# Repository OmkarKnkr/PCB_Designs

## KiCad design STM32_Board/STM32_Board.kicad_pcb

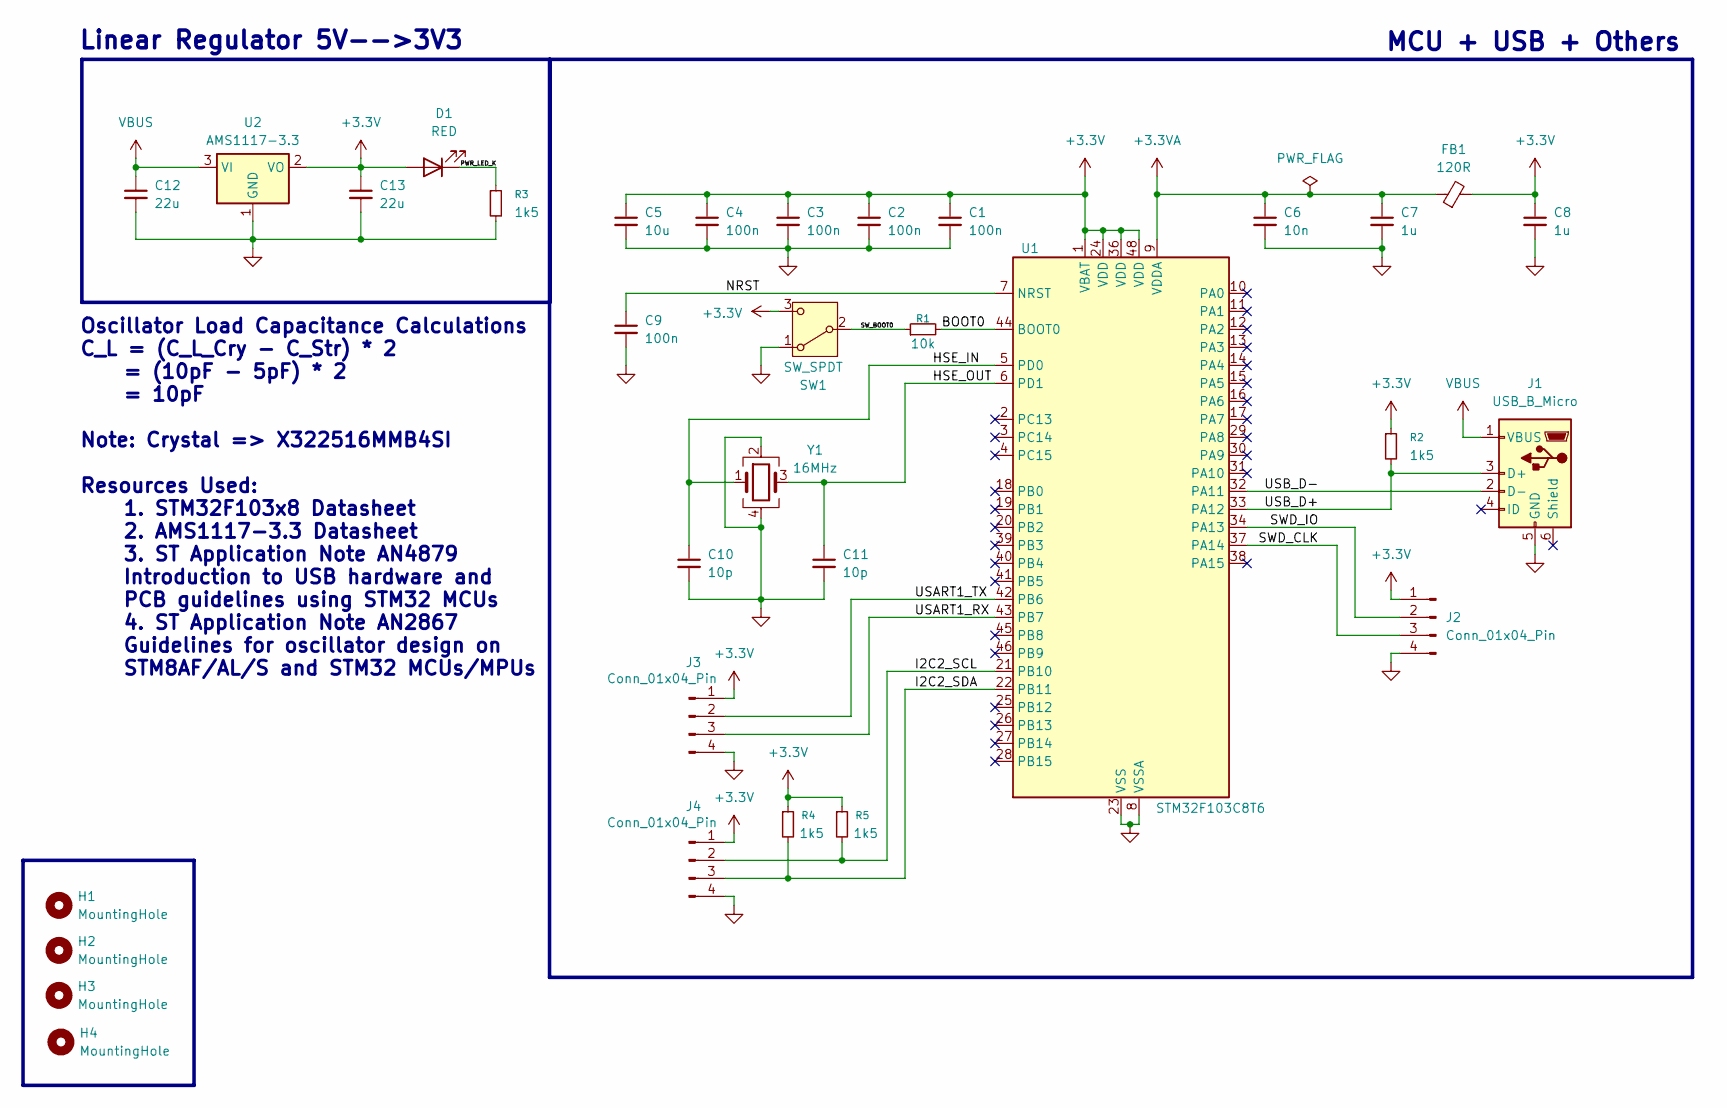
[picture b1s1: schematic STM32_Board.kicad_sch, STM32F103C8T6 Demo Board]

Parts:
C1, C2, C3, C4, C9: 100n; C_0402_1005Metric
C5: 10u; C_0603_1608Metric
C6: 10n; C_0402_1005Metric
C7, C8: 1u; C_0402_1005Metric
C10, C11: 10p; C_0402_1005Metric
C12, C13: 22u; C_0805_2012Metric
D1: RED; LED_0603_1608Metric
FB1: 120R; L_0603_1608Metric
H1, H2, H3, H4: MountingHole; MountingHole_2.2mm_M2
J1: USB_B_Micro; USB_Micro-B_Wuerth_629105150521
J2, J3, J4: Conn_01x04_Pin; PinHeader_1x04_P2.54mm_Vertical
R1: 10k; R_0402_1005Metric
R2, R3, R4, R5: 1k5; R_0402_1005Metric
SW1: SW_SPDT; SW_SPDT_PCM12
U1: STM32F103C8T6; LQFP-48_7x7mm_P0.5mm
U2: AMS1117-3.3; SOT-223-3_TabPin2
Y1: 16MHz; Crystal_SMD_3225-4Pin_3.2x2.5mm

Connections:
+3.3V: C1.1, C2.1, C3.1, C4.1, C5.1, C8.1, C13.1, D1.2 (A), FB1.2, J2.1, J3.1, J4.1, R2.1, R4.1, R5.1, SW1.3 (C), U1.1 (VBAT), U1.24 (VDD), U1.36 (VDD), U1.48 (VDD), U2.2 (VO)
+3.3VA: C6.1, C7.1, FB1.1, U1.9 (VDDA)
/BOOT0: R1.2, U1.44 (BOOT0)
/HSE_IN: C10.1, U1.5 (PD0), Y1.1
/HSE_OUT: C11.1, U1.6 (PD1), Y1.3
/I2C2_SCL: J4.2, R5.2, U1.21 (PB10)
/I2C2_SDA: J4.3, R4.2, U1.22 (PB11)
/NRST: C9.1, U1.7 (NRST)
/PWR_LED_K: D1.1 (K), R3.1
/SWD_CLK: J2.3, U1.37 (PA14)
/SWD_IO: J2.2, U1.34 (PA13)
/SW_BOOT0: R1.1, SW1.2 (B)
/USART1_RX: J3.3, U1.43 (PB7)
/USART1_TX: J3.2, U1.42 (PB6)
/USB_D+: J1.3 (D+), R2.2, U1.33 (PA12)
/USB_D-: J1.2 (D-), U1.32 (PA11)
GND: C1.2, C2.2, C3.2, C4.2, C5.2, C6.2, C7.2, C8.2, C9.2, C10.2, C11.2, C12.2, C13.2, J1.5 (GND), J2.4, J3.4, J4.4, R3.2, SW1.1 (A), U1.8 (VSSA), U1.23 (VSS), U1.35 (VSS), U1.47 (VSS), U2.1 (GND), Y1.2, Y1.4
VBUS: C12.1, J1.1 (VBUS), U2.3 (VI)

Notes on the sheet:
Oscillator Load Capacitance Calculations C_L = (C_L_Cry - C_Str) * 2 = (10pF - 5pF) * 2 = 10pF Note: Crystal => X322516MMB4SI Resources Used: 1. STM32F103x8 Datasheet 2. AMS1117-3.3 Datasheet 3. ST Application Note AN4879 Introduction to USB hardware and PCB guidelines using STM32 MCUs 4. ST Applic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
MCU + USB + Others
Linear Regulator 5V-->3V3

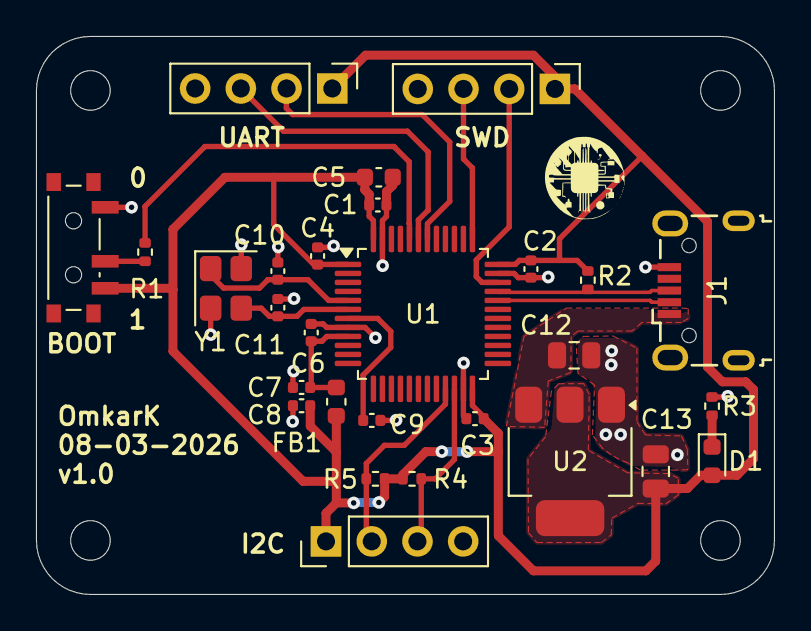
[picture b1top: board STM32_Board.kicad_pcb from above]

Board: 2 copper layers, 41.0 x 31.0 mm, 32 parts (0 on the bottom side), 18 nets.

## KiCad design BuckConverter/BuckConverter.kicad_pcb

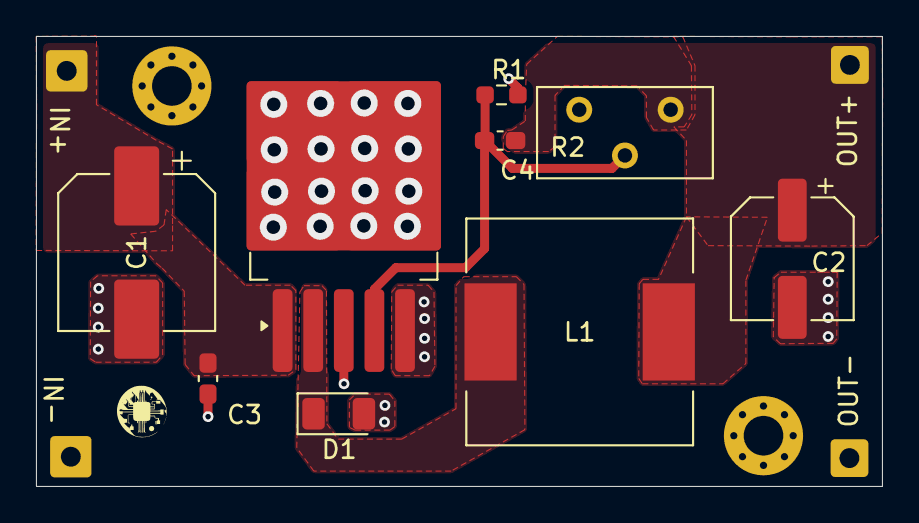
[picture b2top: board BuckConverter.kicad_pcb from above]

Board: 2 copper layers, 47.0 x 25.0 mm, 13 parts (0 on the bottom side), 5 nets.

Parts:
C1: 470u; CP_Elec_8x10.5
C2: 220u; CP_Elec_6.3x7.7
C3, C4: 100n; C_0603_1608Metric_Pad1.08x0.95mm_HandSolder
D1: 1N5825; D_1206_3216Metric
IN+: IN+; SolderWire-0.5sqmm_1x01_D0.9mm_OD2.3mm
IN-: IN-; SolderWire-0.5sqmm_1x01_D0.9mm_OD2.3mm
L1: 33u; L_12x12mm_H4.5mm
OUT+: OUT+; SolderWire-0.5sqmm_1x01_D0.9mm_OD2.1mm
OUT-: OUT-; SolderWire-0.5sqmm_1x01_D0.9mm_OD2.1mm
R1: 330; R_0603_1608Metric_Pad0.98x0.95mm_HandSolder
R2: 10k; Potentiometer_Bourns_3296Y_Vertical
U1: LM2596S-ADJ; TO-263-5_TabPin3

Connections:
/Pw_In: C1.1, C3.1, IN+.1, U1.1 (VIN)
/Pw_Out: C2.1, C4.2, L1.2, OUT+.1, R2.1
/Pw_OutL: D1.1 (K), L1.1, U1.2 (OUT)
GND: C1.2, C2.2, C3.2, D1.2 (A), IN-.1, OUT-.1, R1.1, U1.3 (GND), U1.5 (~ON/OFF)
unnamed: C4.1, R1.2, R2.2, U1.4 (FB)

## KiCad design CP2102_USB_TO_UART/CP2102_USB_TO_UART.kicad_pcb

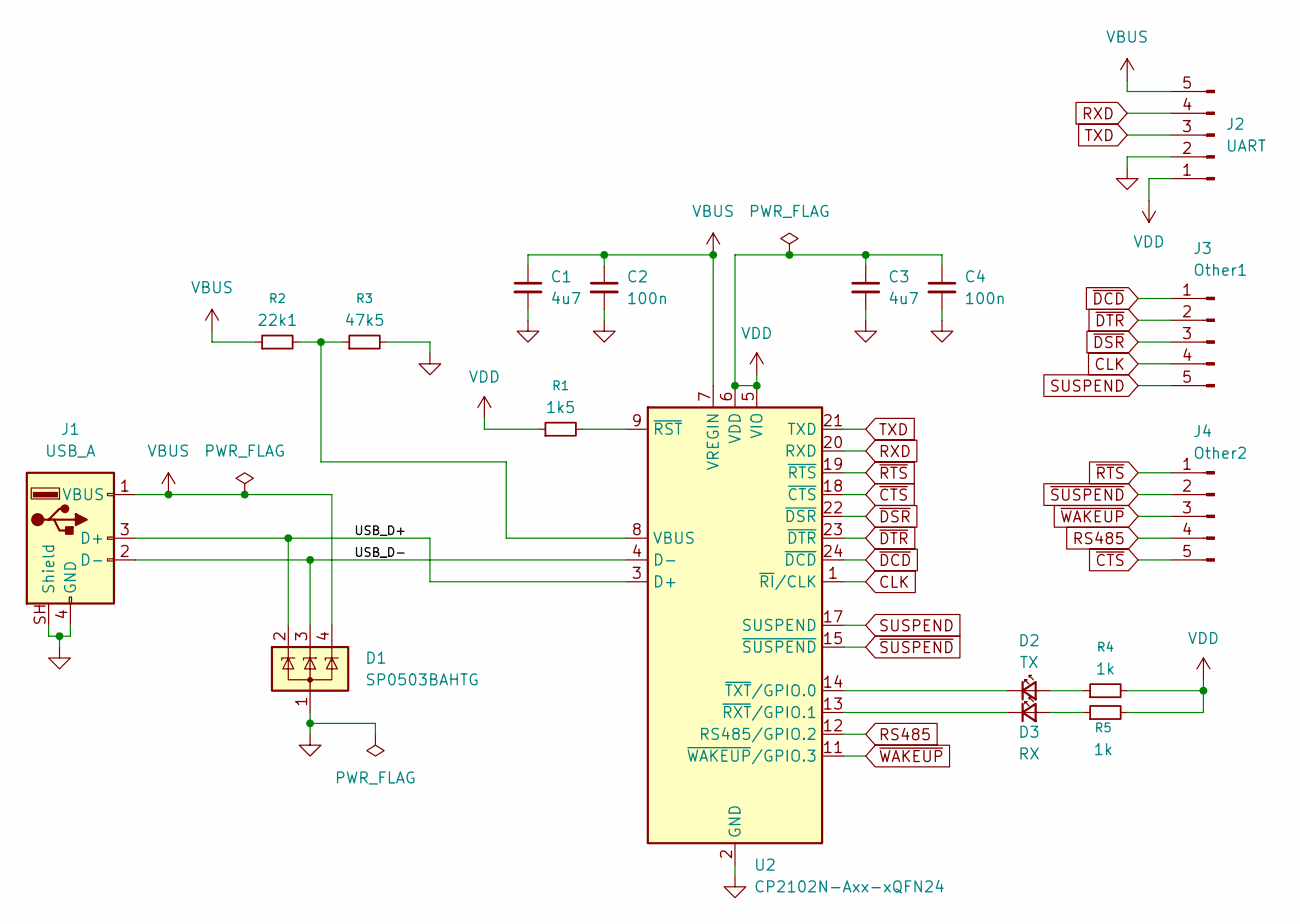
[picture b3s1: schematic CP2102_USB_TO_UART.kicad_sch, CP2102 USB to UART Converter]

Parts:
C1, C3: 4u7; C_0603_1608Metric
C2, C4: 100n; C_0402_1005Metric
D1: SP0503BAHTG; SOT-143
D2: TX; LED_0603_1608Metric
D3: RX; LED_0603_1608Metric
J1: USB_A; USB_A_CNCTech_1001-011-01101_Horizontal
J2: UART; PinHeader_1x05_P2.54mm_Horizontal
J3: Other1; PinHeader_1x05_P2.54mm_Vertical
J4: Other2; PinHeader_1x05_P2.54mm_Vertical
R1: 1k5; R_0603_1608Metric
R2: 22k1; R_0603_1608Metric
R3: 47k5; R_0603_1608Metric
R4, R5: 1k; R_0603_1608Metric
U2: CP2102N-Axx-xQFN24; QFN-24-1EP_4x4mm_P0.5mm_EP2.6x2.6mm

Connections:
/USB_D+: D1.2 (K), J1.3 (D+), U2.3 (D+)
/USB_D-: D1.3 (K), J1.2 (D-), U2.4 (D-)
CLK: J3.4, U2.1 (~RI/CLK)
GND: C1.2, C2.2, C3.2, C4.2, D1.1 (A), J1.4 (GND), J1.SH (Shield), J2.2, R3.2, U2.2 (GND), U2.25 (GND)
unnamed: D2.2 (A), R4.1
unnamed: D2.1 (K), U2.14 (~TXT/GPIO.0)
unnamed: D3.2 (A), R5.1
unnamed: D3.1 (K), U2.13 (~RXT/GPIO.1)
unnamed: R2.2, R3.1, U2.8 (VBUS)
unnamed: R1.2, U2.9 (~RST)
RS485: J4.4, U2.12 (RS485/GPIO.2)
RXD: J2.4, U2.20 (RXD)
SUSPEND: J3.5, U2.17 (SUSPEND)
TXD: J2.3, U2.21 (TXD)
VBUS: C1.1, C2.1, D1.4 (K), J1.1 (VBUS), J2.5, R2.1, U2.7 (VREGIN)
VDD: C3.1, C4.1, J2.1, R1.1, R4.2, R5.2, U2.5 (VIO), U2.6 (VDD)
~CTS: J4.5, U2.18 (~CTS)
~DCD: J3.1, U2.24 (~DCD)
~DSR: J3.3, U2.22 (~DSR)
~DTR: J3.2, U2.23 (~DTR)
~RTS: J4.1, U2.19 (~RTS)
~SUSPEND: J4.2, U2.15 (~SUSPEND)
~WAKEUP: J4.3, U2.11 (~WAKEUP/GPIO.3)

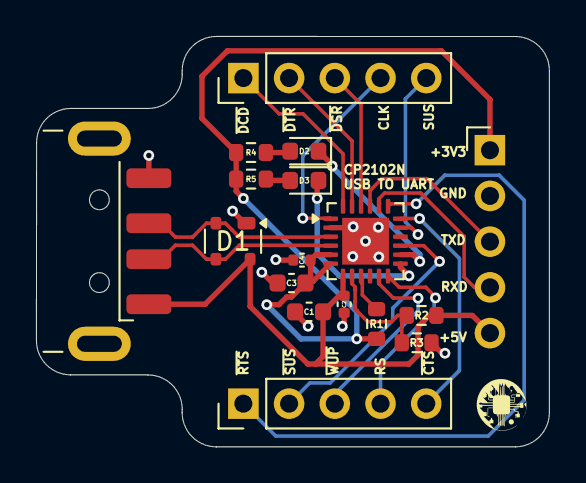
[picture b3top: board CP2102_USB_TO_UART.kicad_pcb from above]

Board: 4 copper layers, 28.5 x 22.8 mm, 17 parts (0 on the bottom side), 23 nets.

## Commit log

2026-05-02 Adding Design Files
2026-05-02 Adding Initial Design Files
